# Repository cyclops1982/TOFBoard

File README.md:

# TOFBoard

This is a simple ToF board with RJ45 connect. The connect is to make it easier to connect. It is NOT a network device.

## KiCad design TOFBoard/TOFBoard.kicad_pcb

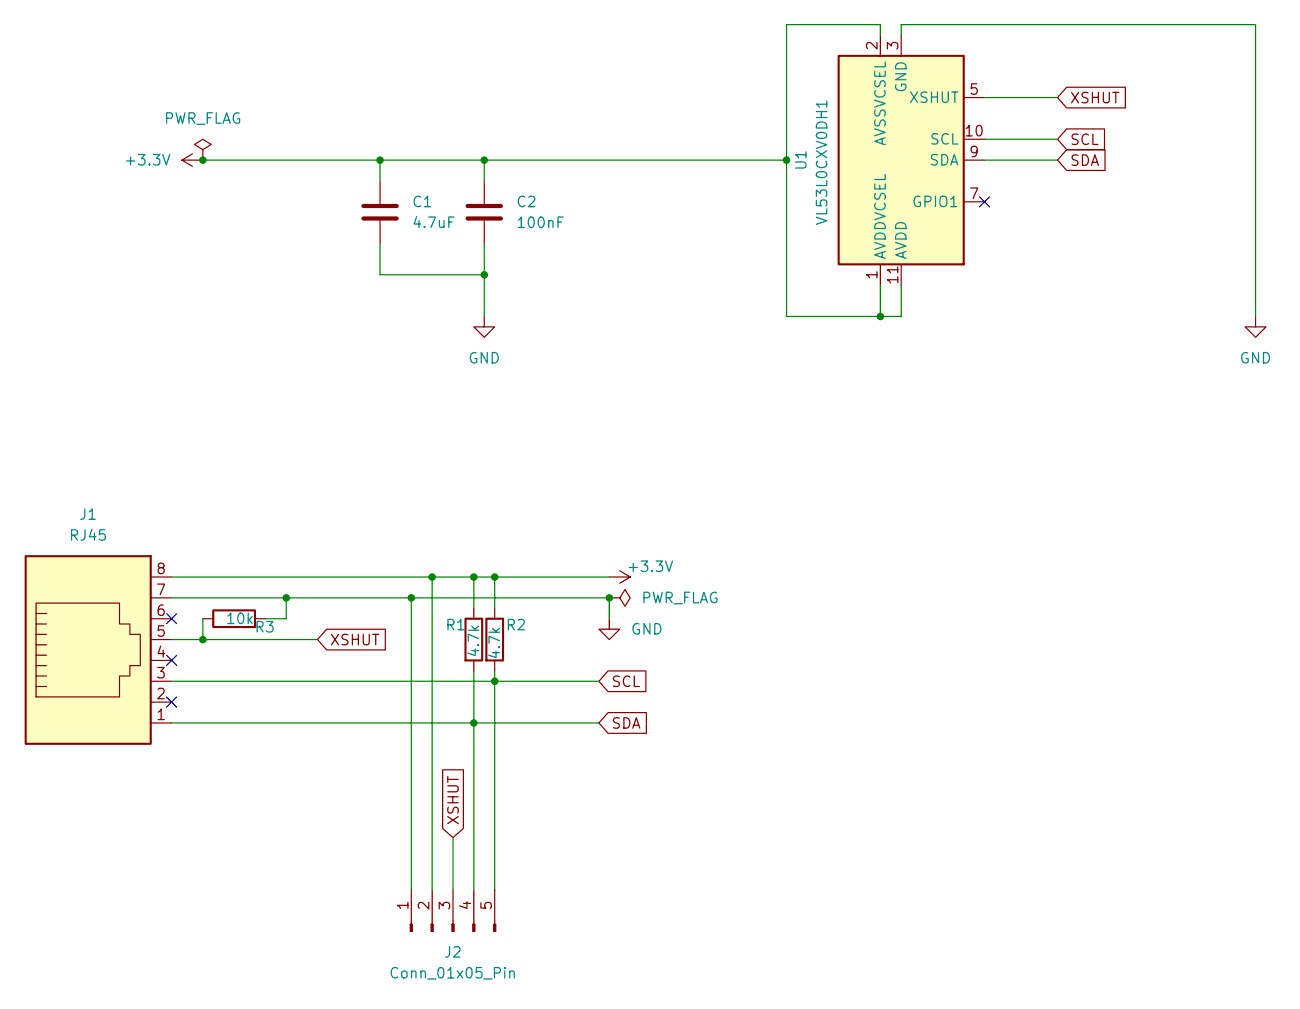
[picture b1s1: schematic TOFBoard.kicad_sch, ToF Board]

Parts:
C1: 4.7uF; C_1206_3216Metric_Pad1.33x1.80mm_HandSolder
C2: 100nF; C_1206_3216Metric_Pad1.33x1.80mm_HandSolder
J1: RJ45; RJ45_Amphenol_54602-x08_Horizontal
J2: Conn_01x05_Pin; PinHeader_1x05_P2.54mm_Vertical
R1, R2: 4.7k; R_1206_3216Metric_Pad1.30x1.75mm_HandSolder
R3: 10k; R_1206_3216Metric_Pad1.30x1.75mm_HandSolder
U1: VL53L0CXV0DH1; ST_VL53L1x

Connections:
+3.3V: C1.1, C2.1, J1.8, J2.2, R1.1, R2.1, U1.1 (AVDDVCSEL), U1.2 (AVSSVCSEL), U1.11 (AVDD)
GND: C1.2, C2.2, J1.7, J2.1, R3.2, U1.3 (GND), U1.4 (GND), U1.6 (GND), U1.12 (GND)
SCL: J1.3, J2.5, R2.2, U1.10 (SCL)
SDA: J1.1, J2.4, R1.2, U1.9 (SDA)
XSHUT: J1.5, J2.3, R3.1, U1.5 (XSHUT)

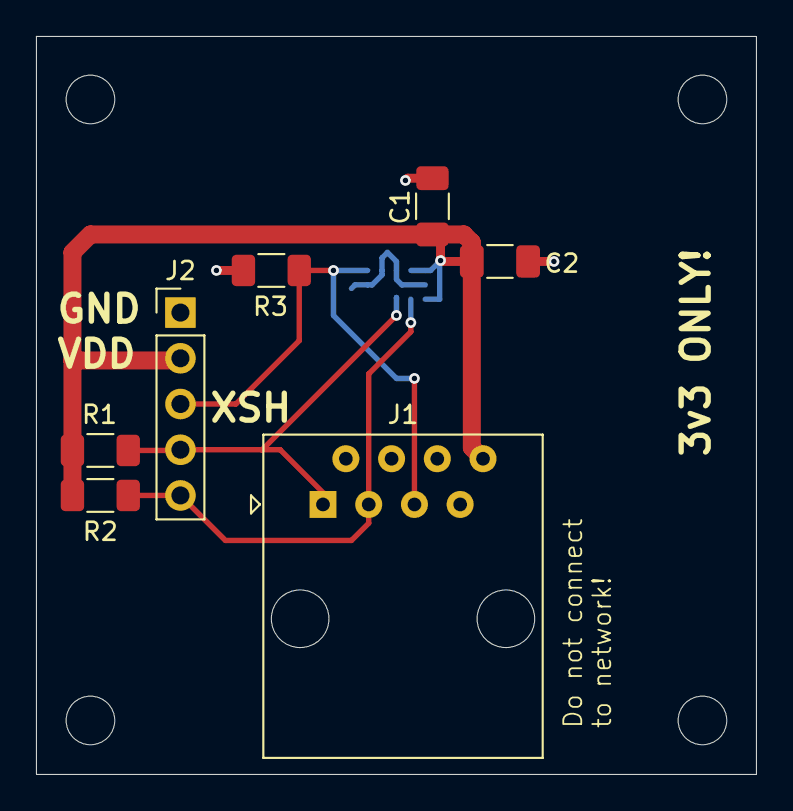
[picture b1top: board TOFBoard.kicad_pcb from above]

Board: 2 copper layers, 40.0 x 41.0 mm, 9 parts (1 on the bottom side), 5 nets.

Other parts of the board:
REF: MountingHole_2.7mm_M2.5

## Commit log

2025-01-21 Initial commit (readme)
2025-01-21 Gitignore added
2025-01-21 Add kicad files
2025-01-21 Add pro file
2025-01-21 Add prl file
2025-02-05 Add Simple mount for enclosure
2025-02-05 Add Subodule for VL53L4CX
2025-02-05 Add platformio project to test things
2025-02-05 Intellicens working again
2025-02-07 Updated code with more output, and some caliberation that should make it better.
2025-02-07 Add caliberation data, to try tomorrow.
2025-02-24 New design
2025-03-03 Upgrade to KiCad 9 & board size
2025-03-09 Rework after review
2025-03-09 Add comments on sheet
2025-03-10 Small changes, but should be done.
2025-03-16 Add pull-up's to SDA/SCL
2025-03-16 Add pull-ups to PCB
2025-03-25 Changes, rework, nicer.
    also, lots of weird mistakes removed.
